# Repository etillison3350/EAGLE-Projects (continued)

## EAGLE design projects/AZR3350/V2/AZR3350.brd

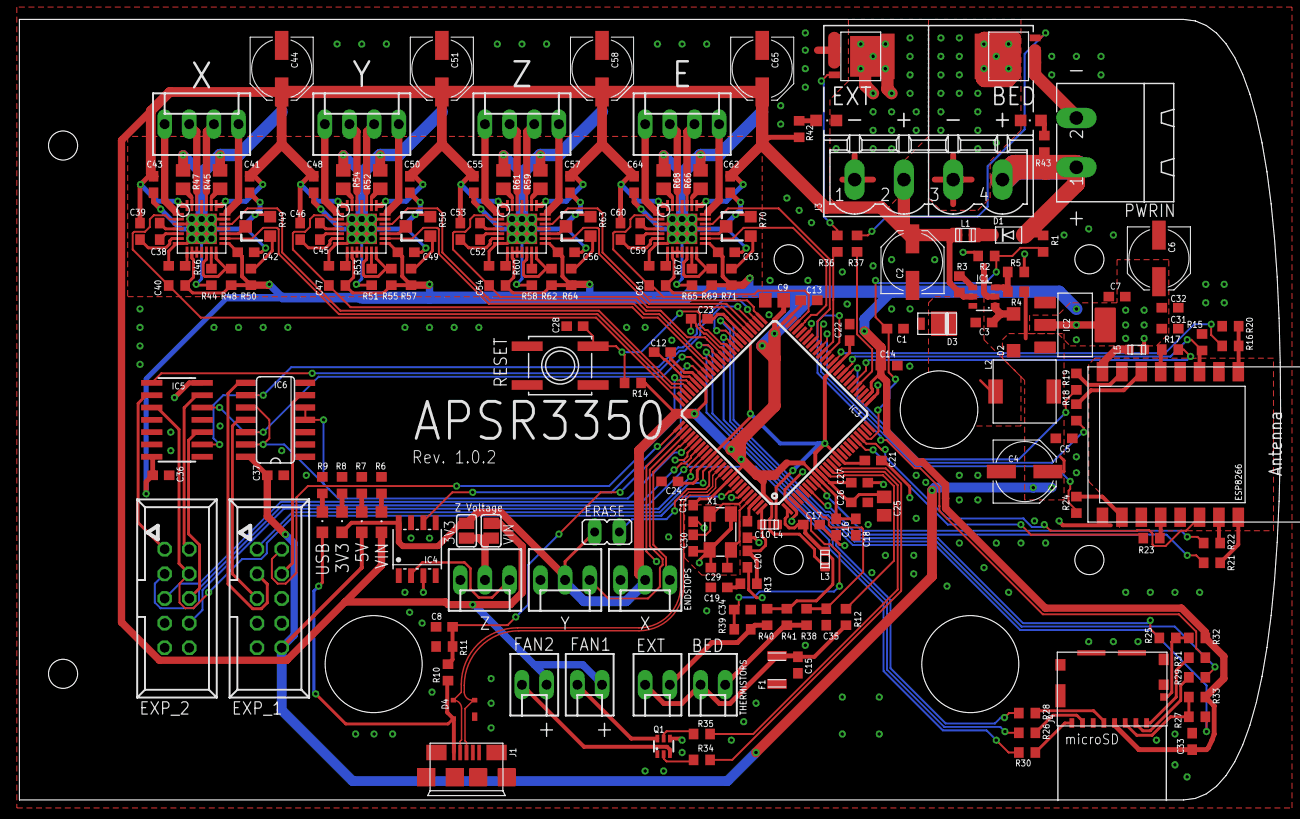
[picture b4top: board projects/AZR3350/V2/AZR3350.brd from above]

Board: 2 copper layers, 130.0 x 80.5 mm, 188 parts (0 on the bottom side), 169 nets.

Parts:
3V3, 5V: CHIPLED_0805
BED: KK-254-2; MOLEX-KK-254-2
BED_L: CHIPLED_0805
C1, C28: 10n; C0603
C2, C6: 10uF; PANASONIC_D
C3, C8, C10, C11, C12, C13, C14, C16, C17, C20, C21, C22, C23, C24, C26, C37, C38, C39, C41, C43, C45, C46, C48, C50, C52, C53, C55, C57, C59, C60, C62, C64: 100n; C0603
C4: 47u; PANASONIC_D
C5, C7: 4.7uF; C0603
C9, C25: 10u; C0805
C15, C34, C35, C36: 2.2u; C0603
C18, C31, C32: 10u; C0603
C19: 4u7; C0603
C27: 2.2u 0.1-10ohm ESR; C0603
C29, C30: 10p; C0603
C33: 2K2; C0603
C40, C42, C47, C49, C54, C56, C61, C63: 220n; C0603
C44, C51, C58, C65: 100u; PANASONIC_D
D1: BYS10-45-E3; SOD-123FL
D2: CD1206-S01575; SOD123
D3: SS1P3L; DO220AAL
D4: PRTR5V0U2XB; SOT143B
E: KK-254-4; MOLEX-KK-254-4
ERASE: JP1
ESP8266: ESP-12
EXP_1, EXP_2: 057-010-1
EXT: KK-254-2; MOLEX-KK-254-2
EXT_L: CHIPLED_0805
F1: MC36207
FAN1, FAN2: KK-254-2; MOLEX-KK-254-2
IC1: LM2734Y; SOT23-6
IC2: LDO-TS1117CW-3V3; SOT223
IC3: ATSAM4S8C; LQFP100
IC4: SI87XXIS; SOIC08-FAIRCHILD
IC5: 74HC125; SO14
IC6: 74S08D; SO14
IC7, IC8, IC9, IC10: A4988; QFN28-TP
J1: ZX62-AB-5PA; USB-MICRO-10103594
J3: MSTBV4
J4: MOLEX-105162-001; MOLEX-105162
L1: MH2029-300Y; C0805
L2: 10uH-SRR0604-100ML; SRR0604
L3, L4: 10uH 100MHz; C0603
L5: 4n7H; C0603
PWRIN: MSTBA2
Q1: NX138BKS; SOT363_PHILIPS
Q2, Q3: BUK9Y53-100B; SOT-669
R1, R11: 47K; R0603
R2, R6, R15, R42, R43: 4K7; R0603
R3: 100k; R0603
R4: 5.53k; R0603
R5: 10k; R0603
R7, R9, R20, R21, R23, R24: 2K2; R0603
R8, R36, R37: 180R; R0603
R10: 27K; R0603
R12, R14, R32, R33, R38, R39, R44, R46, R51, R53, R58, R60, R65, R67: 10K; R0603
R13: 1R; R0603
R16, R22: 470R; R0603
R17, R18, R19: 47R; R0603
R25, R26, R27, R29, R30, R31: 220R; R0603
R28: 100R; R0603
R34, R35: 1K; R0603
R40, R41: 4K7 0.1%; R0603
R45, R47, R52, R54, R59, R61, R66, R68: 0R2; R0805
R48, R55, R62, R69: 100K; R0603
R49, R56, R63, R70: 10K; RTRIM3103
R50, R57, R64, R71: 20K; R0603
RESET: EVQQ2
SJ1, SJ2: SJ
USB: CHIPLED_0805
VIN: CHIPLED_0805
X: KK-254-4; MOLEX-KK-254-4
X1: 12MHz; 5.0X3.2_KX-9A
X_STOP: KK-254-3; MOLEX-KK-254-3
Y: KK-254-4; MOLEX-KK-254-4
Y_STOP: KK-254-3; MOLEX-KK-254-3
Z: KK-254-4; MOLEX-KK-254-4
Z_STOP: KK-254-3; MOLEX-KK-254-3

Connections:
3V3_LED: 3V3.C, R8.1
5V_LED: 5V.C, R7.1
24V_LED: R6.1, VIN.C
+3V3: 3V3.A, C6.+, C7.2, C9.2, C10.2, C11.2, C12.2, C13.2, C14.2, C16.1, C18.1, C31.1, C32.1, C33.1, C36.1, C42.1, C49.1, C56.1, C63.1, ERASE.1, IC2.2, IC2.4, IC3.10, IC3.27, IC3.50, IC3.69, IC3.91, IC3.98, IC4.8, IC5.14, IC7.9, IC7.10, IC7.11, IC7.15, IC8.9, IC8.10, IC8.11, IC8.15, IC9.9, IC9.10, IC9.11, IC9.15, IC10.9, IC10.10, IC10.11, IC10.15, J4.P4, L3.2, L5.1, R14.2, R32.2, R33.2, R46.2, R48.2, R50.2, R53.2, R55.2, R57.2, R60.2, R62.2, R64.2, R67.2, R69.2, R71.2, SJ1.1, X_STOP.2, Y_STOP.2
+5V: 5V.A, C4.+, C5.1, C37.1, D2.A, EXP_1.10, IC2.3, IC6.14, L2.P$2, R4.1
+24V: C2.+, C39.2, C41.1, C43.1, C44.+, C46.2, C48.1, C50.1, C51.+, C53.2, C55.1, C57.1, C58.+, C60.2, C62.1, C64.1, C65.+, FAN1.1, FAN2.1, IC1.5, IC7.22, IC7.28, IC8.22, IC8.28, IC9.22, IC9.28, IC10.22, IC10.28, J3.2, L1.2, R3.1, R42.2, SJ2.1, VIN.A
ADVREF: C17.1, IC3.1, L3.1, R40.2, R41.2
BED: IC3.30, R37.1
BED_D: BED_L.C, J3.3, Q3.EXP, Q3.MB
BED_G: Q3.4, R37.2
BED_L: BED_L.A, R43.1
BEEPER: EXP_1.1, IC3.86
BOOST: C3.1, D2.C, IC1.1
BTN_EN1: EXP_2.5, IC3.82
BTN_EN2: EXP_2.3, IC3.83
BTN_ENC: EXP_1.2, IC3.71
CLK: J4.P5, R28.2
CMD: J4.P3, R27.2, R33.1
CP1E: C59.1, IC10.4
CP1X: C38.1, IC7.4
CP1Y: C45.1, IC8.4
CP1Z: C52.1, IC9.4
CP2E: C59.2, IC10.5
CP2X: C38.2, IC7.5
CP2Y: C45.2, IC8.5
CP2Z: C52.2, IC9.5
DAT0: J4.P7, R26.2
DAT1: J4.P8, R30.2
DAT2: J4.P1, R31.2
DAT3: J4.P2, R29.2
DET: J4.P9, R25.2, R32.1
EDR_CONN: ESP8266.12, R23.2
EMOT1A: E.3, IC10.24
EMOT1B: E.4, IC10.21
EMOT2A: E.2, IC10.26
EMOT2B: E.1, IC10.1
ERASE: ERASE.2, IC3.87
ESP_CS: ESP8266.10, R24.2
ESP_DATA_RDY: IC3.21, R23.1
ESP_EN: ESP8266.3, IC3.34, R15.1
ESP_MISO: ESP8266.6, R18.1
ESP_MOSI: ESP8266.7, R19.1
ESP_RESET: ESP8266.1, R16.2, R20.2
ESP_RST: IC3.37, R16.1
ESP_SPCK: ESP8266.5, R17.1
ESP_URDX: ESP8266.16, R21.2
ESP_UTDX: ESP8266.15, R22.2
ESP_VIN: ESP8266.8, L5.2
EXT_D: EXT_L.C, J3.1, Q2.EXP, Q2.MB
EXT_G: Q2.4, R36.2
EXT_L: EXT_L.A, R42.1
E_DIR: IC3.43, IC10.19
E_EN: IC3.48, IC10.2, R67.1
E_STEP: IC3.47, IC10.16
FAN1: IC3.14, R34.1
FAN1_D: FAN1.2, Q1.6
FAN1_G: Q1.2, R34.2
FAN2: IC3.13, R35.1
FAN2_D: FAN2.2, Q1.3
FAN2_G: Q1.5, R35.2
FB: IC1.3, R4.2, R5.1
GND: C1.2, C2.-, C4.-, C5.2, C6.-, C7.1, C8.1, C9.1, C10.1, C11.1, C12.1, C13.1, C14.1, C15.2, C16.2, C17.2, C18.2, C19.2, C20.2, C21.2, C22.2, C23.2, C24.2, C25.2, C26.2, C27.2, C28.2, C29.2, C30.2, C31.2, C32.2, C33.2, C34.2, C35.2, C36.2, C37.2, C40.2, C41.2, C42.2, C43.2, C44.-, C47.2, C48.2, C49.2, C50.2, C51.-, C54.2, C55.2, C56.2, C57.2, C58.-, C61.2, C62.2, C63.2, C64.2, C65.-, D3.P$2, D4.1, ESP8266.9, EXP_1.9, EXP_2.9, F1.2, IC1.2, IC2.1, IC3.2, IC3.26, IC3.45, IC3.61, IC3.70, IC3.77, IC3.95, IC4.3, IC4.5, IC5.1, IC5.4, IC5.7, IC5.12, IC5.13, IC6.1, IC6.2, IC6.7, IC7.3, IC7.7, IC7.18, IC7.20, IC7.25, IC7.PAD, IC8.3, IC8.7, IC8.18, IC8.20, IC8.25, IC8.PAD, IC9.3, IC9.7, IC9.18, IC9.20, IC9.25, IC9.PAD, IC10.3, IC10.7, IC10.18, IC10.20, IC10.25, IC10.PAD, J1.GND, J4.G1, J4.G2, J4.G3, J4.G4, J4.P6, PWRIN.2, Q1.1, Q1.4, Q2.1, Q2.2, Q2.3, Q3.1, Q3.2, Q3.3, R2.1, R5.2, R6.2, R7.2, R8.2, R9.2, R11.2, R15.2, R20.1, R44.2, R45.1, R47.1, R49.3, R51.2, R52.1, R54.1, R56.3, R58.2, R59.1, R61.1, R63.3, R65.2, R66.1, R68.1, R70.3, RESET.B, RESET.B', X1.2, X1.4, X_STOP.3, Y_STOP.3, Z_STOP.3
HOTEND: IC3.40, R36.1
LCD_CS: IC3.80, IC6.4, IC6.5, IC6.10, IC6.13
LCD_CS_BUF: EXP_1.4, IC6.6
LCD_MISO: IC3.53, IC5.8
LCD_MISO_BUF: EXP_2.1, IC5.9
LCD_MOSI: IC3.52, IC5.2, IC6.9
LCD_MOSI_BUF: EXP_1.3, IC6.8
LCD_RST: EXP_2.8, IC3.84
LCD_SCK: IC3.67, IC5.5, IC6.12
LCD_SCK_BUF: EXP_1.5, IC6.11
LCD_SD_CS: EXP_2.4, IC3.93, IC5.10
MCCDA: IC3.59, R27.1
MCCK: IC3.63, R28.1
MCDA0: IC3.64, R26.1
MCDA1: IC3.81, R30.1
MCDA2: IC3.39, R31.1
MCDA3: IC3.57, R29.1
MISO: IC3.41, R18.2
MOSI: IC3.33, R19.2
unnamed: C19.1, R13.1
NPCS0: IC3.42, R24.1
PWR_FAIL_DET: C1.1, IC3.23, R1.1, R2.2
REFE: IC10.17, R70.2
REFE-IN: R70.1, R71.1
REFX: IC7.17, R49.2
REFX-IN: R49.1, R50.1
REFY: IC8.17, R56.2
REFY-IN: R56.1, R57.1
REFZ: IC9.17, R63.2
REFZ-IN: R63.1, R64.1
RESET: C28.1, IC3.60, R14.1, RESET.A'
ROSCE: IC10.13, R65.1
ROSCX: IC7.13, R44.1
ROSCY: IC8.13, R51.1
ROSCZ: IC9.13, R58.1
RSTE: IC10.12, IC10.14, R69.1
RSTX: IC7.12, IC7.14, R48.1
RSTY: IC8.12, IC8.14, R55.1
RSTZ: IC9.12, IC9.14, R62.1
SAM_TFR_RDY: ESP8266.14, IC3.22
SD_CD: IC3.58, R25.1
SD_MOSI_BUF: EXP_2.6, IC5.3
SD_SCK_BUF: EXP_2.2, IC5.6
SHDN: IC1.4, R3.2
SNS1E: IC10.23, R66.2
SNS1X: IC7.23, R45.2
SNS1Y: IC8.23, R52.2
SNS1Z: IC9.23, R59.2
SNS2E: IC10.27, R68.2
SNS2X: IC7.27, R47.2
SNS2Y: IC8.27, R54.2
SNS2Z: IC9.27, R61.2
SPCK: IC3.31, R17.2
SW: C3.2, D3.P$1, IC1.6, L2.P$1
T_BED: C35.1, IC3.5, R38.1
T_BED_IN: BED.1, R38.2, R41.1
T_EXT: C34.1, IC3.3, R39.1
T_EXT_IN: EXT.1, R39.2, R40.1
URXD1: IC3.7, R21.1
USB_LED: R9.1, USB.C
USB_N: D4.3, IC3.88, J1.D-
USB_P: D4.2, IC3.89, J1.D+
USB_PWR_MON: C8.2, IC3.68, R10.2, R11.1
UTXD1: IC3.9, R22.1
VBUS: D4.4, J1.VBUS, R10.1, USB.A
VCPE: C60.1, IC10.6
VCPX: C39.1, IC7.6
VCPY: C46.1, IC8.6
VCPZ: C53.1, IC9.6
VDDOUT: C21.1, C22.1, C23.1, C24.1, C25.1, C26.1, C27.1, IC3.11, IC3.16, IC3.36, IC3.56, IC3.85, L4.2
VDDPLL: C20.1, IC3.100, L4.1, R13.2
VIN: D1.A, J3.4, PWRIN.1, R1.2, R43.2
VIN_F: D1.C, L1.1
VREGE: C61.1, IC10.8
VREGX: C40.1, IC7.8
VREGY: C47.1, IC8.8
VREGZ: C54.1, IC9.8
VSSA: BED.2, C15.1, EXT.2, F1.1, R12.2
VSSA_MON: IC3.12, R12.1
XIN: C29.1, IC3.97, X1.3
XMOT1A: IC7.24, X.3
XMOT1B: IC7.21, X.4
XMOT2A: IC7.26, X.2
XMOT2B: IC7.1, X.1
XOUT: C30.1, IC3.96, X1.1
X_DIR: IC3.72, IC7.19
X_EN: IC3.75, IC7.2, R46.1
X_STEP: IC3.73, IC7.16
X_STOP: IC3.79, X_STOP.1
YMOT1A: IC8.24, Y.3
YMOT1B: IC8.21, Y.4
YMOT2A: IC8.26, Y.2
YMOT2B: IC8.1, Y.1
Y_DIR: IC3.62, IC8.19
Y_EN: IC3.66, IC8.2, R53.1
Y_STEP: IC3.65, IC8.16
Y_STOP: IC3.78, Y_STOP.1
ZMOT1A: IC9.24, Z.3
ZMOT1B: IC9.21, Z.4
ZMOT2A: IC9.26, Z.2
ZMOT2B: IC9.1, Z.1
ZVSEL: SJ1.2, SJ2.2, Z_STOP.2
Z_DIR: IC3.51, IC9.19
Z_EN: IC3.55, IC9.2, R60.1
Z_STEP: IC3.54, IC9.16
Z_STOP: IC3.76, IC4.6
Z_STOP_IN: IC4.2, Z_STOP.1

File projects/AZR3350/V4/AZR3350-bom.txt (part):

Partlist exported from A:/Users/Ethan Tillison/Documents/EAGLE/projects/AZR3350/V4/AZR3350.sch at 07 Mar. 2019 23:55

Qty Value              Device             Package            Parts                                                                                                                                                        Description                                             
1                      ESP-12             ESP-12             ESP8266                                                                                                                                                                                                              
1                      EVQQ2              EVQQ2              RESET                                                                                                                                                                                                                
1                      JP1Q               JP1                ERASE                                                                                                                                                        JUMPER                                                  
6                      LEDCHIPLED_0805    CHIPLED_0805       3V3, 5V, BED_L, EXT_L, USB, VIN                                                                                                                              LED                                                     
1                      PINHD-1X5          1X05               JP3                                                                                                                                                          PIN HEADER                                              
2                      PINHD-1X6/90       1X06/90            JP1, JP2                                                                                                                                                     PIN HEADER                                              
2                      SJ                 SJ                 SJ1, SJ2                                                                                                                                                     SMD solder JUMPER                                       
1                      TE-2041021         2041021            X2                                                                                                                                                                                                                   
8   0R2                R-US_R0805         R0805              R45, R47, R52, R54, R59, R61, R66, R68                                                                                                                       RESISTOR, American symbol                               
4   100K               R-US_R0603         R0603              R48, R55, R62, R69                                                                                                                                           RESISTOR, American symbol                               
1   100R               R-US_R0603         R0603              R28                                                                                                                                                          RESISTOR, American symbol                               
1   100k               R-US_R0603         R0603              R3                                                                                                                                                           RESISTOR, American symbol                               
32  100n               C-EUC0603          C0603              C3, C8, C10, C11, C12, C13, C14, C16, C17, C20, C21, C22, C23, C24, C26, C37, C38, C39, C41, C43, C45, C46, C48, C50, C52, C53, C55, C57, C59, C60, C62, C64 CAPACITOR, European symbol                              
4   100u               CPOL-USD           PANASONIC_D        C44, C51, C58, C65                                                                                                                                           POLARIZED CAPACITOR, American symbol                    
4   10K                R-TRIMM3103        RTRIM3103          R49, R56, R63, R70                                                                                                                                           Trimm resistor                                          
14  10K                R-US_R0603         R0603              R12, R14, R32, R33, R38, R39, R44, R46, R51, R53, R58, R60, R65, R67                                                                                         RESISTOR, American symbol                               
1   10k                R-US_R0603         R0603              R5                                                                                                                                                           RESISTOR, American symbol                               
2   10n                C-EUC0603          C0603              C1, C28                                                                                                                                                      CAPACITOR, European symbol                              
2   10p                C-EUC0603          C0603              C29, C30                                                                                                                                                     CAPACITOR, European symbol                              
3   10u                C-EUC0603          C0603              C18, C31, C32                                                                                                                                                CAPACITOR, European symbol                              
2   10u                C-EUC0805          C0805              C9, C25                                                                                                                                                      CAPACITOR, European symbol                              
2   10uF               CPOL-USD           PANASONIC_D        C2, C6                                                                                                                                                       POLARIZED CAPACITOR, American symbol                    
2   10uH 100MHz        INDUCTOR-0603      C0603              L3, L4                                                                                                                                                       Inductors                                               
1   10uH-SRR0604-100ML 0031_SRR0604-100ML SRR0604            L2                                                                                                                                                           SRR0604-100ML                                           
1   12MHz              CRYSTAL-4PIN       5.0X3.2_KX-9A      X1                                                                                                                                                                                                                   
3   180R               R-US_R0603         R0603              R8, R36, R37                                                                                                                                                 RESISTOR, American symbol                               
3   1K                 R-US_R0603         R0603              R34, R35, R72                                                                                                                                                RESISTOR, American symbol                               
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
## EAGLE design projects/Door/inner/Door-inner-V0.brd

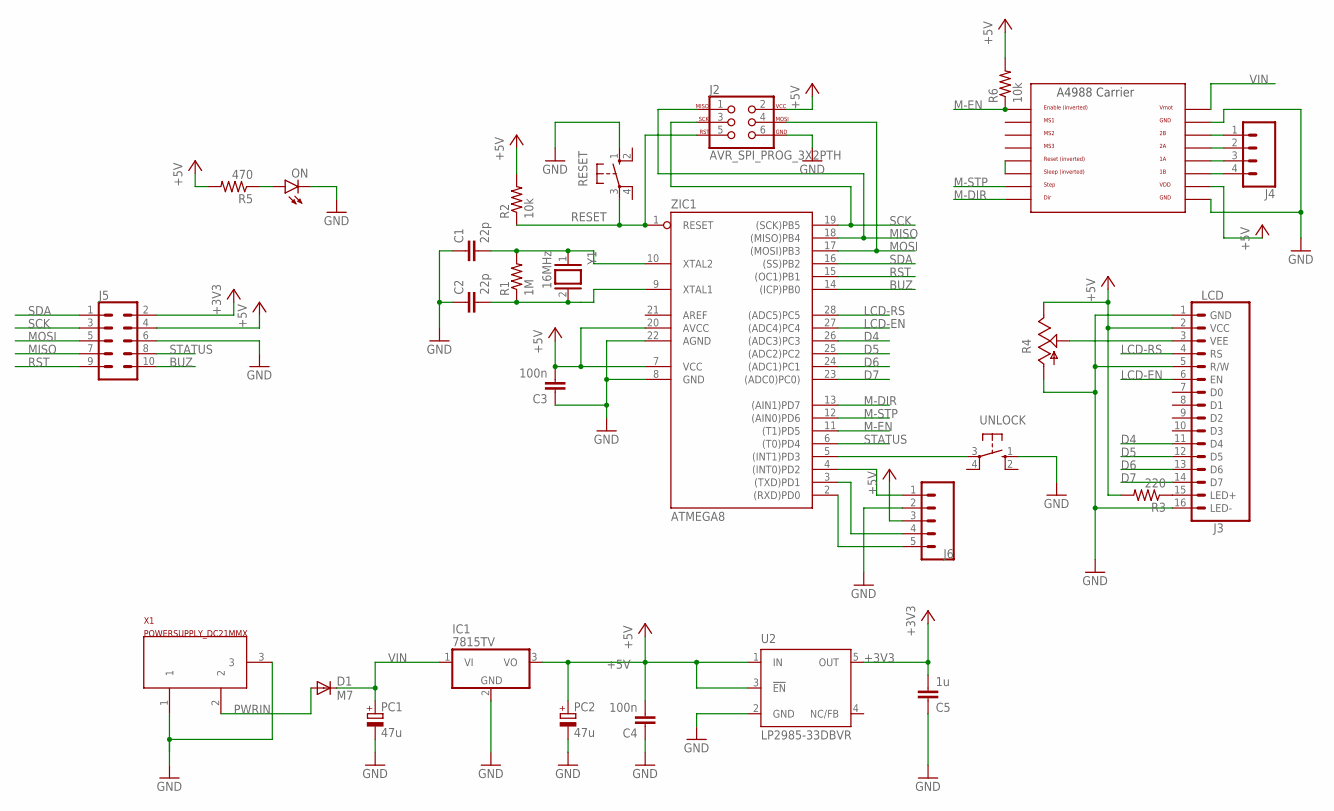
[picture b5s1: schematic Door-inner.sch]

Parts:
C1, C2: 22p; C0805
C3, C4: 100n; C0805
C5: 1u; C0805
D1: M7; SMB
IC1: 7815TV; TO220V
J2: AVR_SPI_PROG_3X2PTH; 2X3
J3: LCD; LCD-16X2
J4: CONN_04; 1X04
J5: CONN_05X2PTH; 2X5
J6: CONN_05; 1X05
ON: LEDCHIPLED_0805; CHIPLED_0805
PC1, PC2: 47u; TT2D5
R1: 1M; R0805
R2, R6: 10k; R0805
R3: 220; R0805
R4: TRIM_US-S63P; S63P
R5: 470; R0805
RESET: 10-XX; B3F-10XX
U2: LP2985-33DBVR; SOT23-DBV
U$1: A4988BREAKOUT
UNLOCK: 10-XX; B3F-10XX
X1: POWERSUPPLY_DC21MMX; POWERSUPPLY_DC-21MM
Y1: 16MHz; QS
ZIC1: ATMEGA8; DIL28-3

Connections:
+3V3: C5.2, J5.2, U2.5 (OUT)
+5V: C3.2, C4.2, IC1.3 (VO), J2.2, J3.2 (VCC), J5.4, J6.3, PC2.+, R2.2, R3.2, R4.E, R5.2, R6.2, U2.1 (IN), U2.3 (!EN), U$1.VDD, ZIC1.7 (VCC), ZIC1.20 (AVCC)
BUZ: J5.10, ZIC1.14 ((ICP)PB0)
D4: J3.11 (D4), ZIC1.26 ((ADC3)PC3)
D5: J3.12 (D5), ZIC1.25 ((ADC2)PC2)
D6: J3.13 (D6), ZIC1.24 ((ADC1)PC1)
D7: J3.14 (D7), ZIC1.23 ((ADC0)PC0))
GND: C1.1, C2.1, C3.1, C4.1, C5.1, IC1.2 (GND), J2.6, J3.1 (GND), J3.5 (R/W), J3.16 (LED-), J5.6, J6.2, ON.C, PC1.-, PC2.-, R4.A, RESET.1 (S), U2.2 (GND), U$1.GND, U$1.GND@0 (GND), UNLOCK.1 (S), X1.1, X1.3, ZIC1.8 (GND), ZIC1.22 (AGND)
LCD-EN: J3.6 (EN), ZIC1.27 ((ADC4)PC4)
LCD-RS: J3.4 (RS), ZIC1.28 ((ADC5)PC5)
M-DIR: U$1.DIR, ZIC1.13 ((AIN1)PD7)
M-EN: R6.1, U$1.EN, ZIC1.11 ((T1)PD5)
M-STP: U$1.STEP, ZIC1.12 ((AIN0)PD6)
MISO: J2.1, J5.7, ZIC1.18 ((MISO)PB4)
MOSI: J2.4, J5.5, ZIC1.17 ((MOSI)PB3)
unnamed: J6.1, ZIC1.4 ((INT0)PD2)
unnamed: J6.4, ZIC1.3 ((TXD)PD1)
unnamed: J6.5, ZIC1.2 ((RXD)PD0)
unnamed: J3.15 (LED+), R3.1
unnamed: J3.3 (VEE), R4.S
unnamed: ON.A, R5.1
unnamed: U$1.RST, U$1.SLP (SLEEP)
unnamed: J4.1, U$1.2B
unnamed: J4.2, U$1.2A
unnamed: J4.3, U$1.1A
unnamed: J4.4, U$1.1B
unnamed: UNLOCK.3, ZIC1.5 ((INT1)PD3)
PWRIN: D1.A, X1.2
RESET: J2.5, R2.1, RESET.3, ZIC1.1 (RESET)
RST: J5.9, ZIC1.15 ((OC1)PB1)
SCK: J2.3, J5.3, ZIC1.19 ((SCK)PB5)
SDA: J5.1, ZIC1.16 ((SS)PB2)
STATUS: J5.8, ZIC1.6 ((T0)PD4)
VIN: D1.C, IC1.1 (VI), PC1.+, U$1.VMOT
XTAL1: C2.2, R1.1, Y1.2, ZIC1.9 (XTAL1)
XTAL2: C1.2, R1.2, Y1.1, ZIC1.10 (XTAL2)

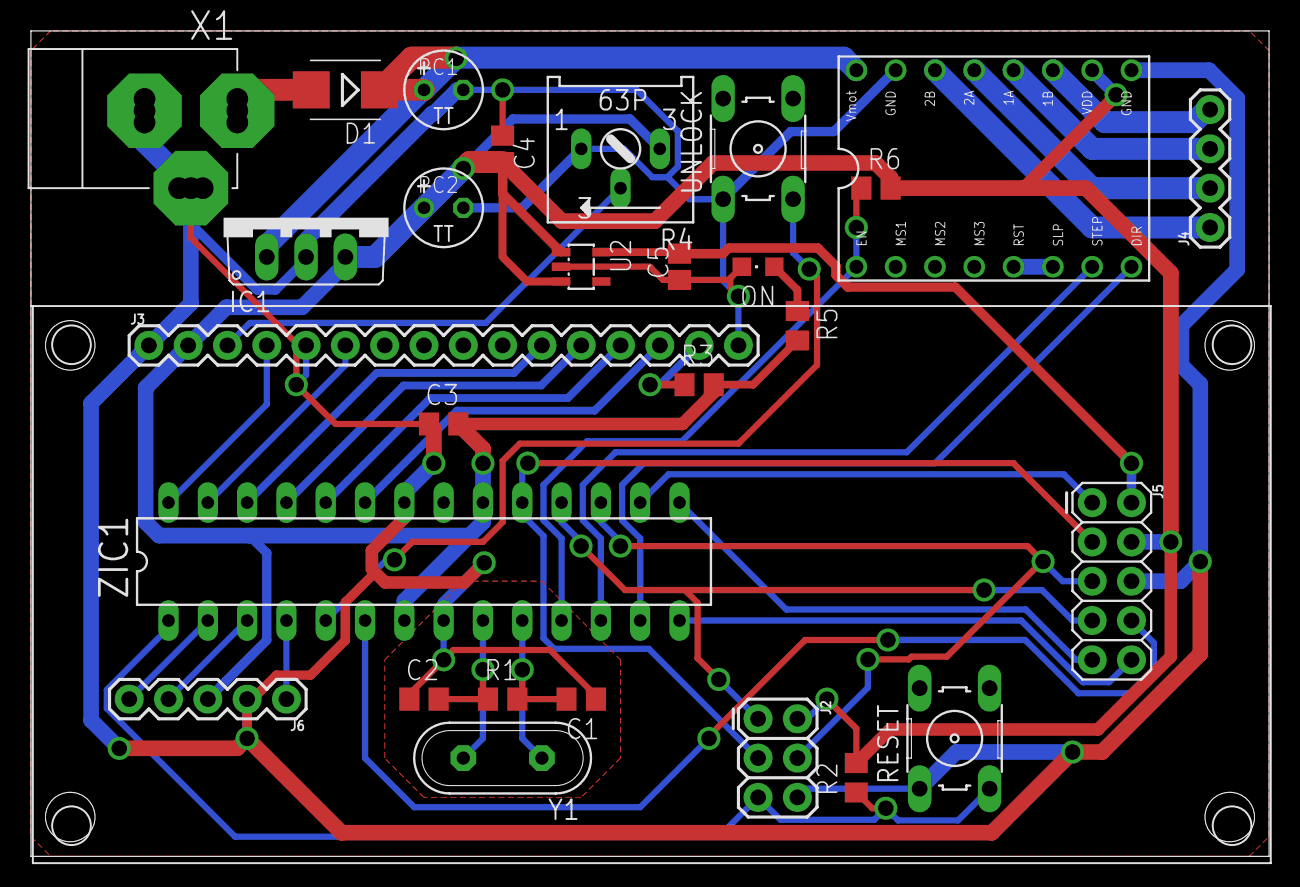
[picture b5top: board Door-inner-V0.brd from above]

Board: 2 copper layers, 80.0 x 53.3 mm, 28 parts (0 on the bottom side), 36 nets.
